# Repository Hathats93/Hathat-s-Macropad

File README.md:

# Hathats' Macropad

# Complete case with switches and keycaps installed

# Bare case (top and bottom)

# PCB schematic

# PCB layout

##  Bill of Materials/BOM
List of all parts used in my hackpad:

| Part | Quantity | Description | 
|------|----------|-------------|
| Mechanical Key Switches | 11 | MX-style switches |
| DSA Keycaps | 11 | Compatible with MX switches | 
| Seeed XIAO RP2040 | 1 | Microcontroller | 
| EC11 Rotary Encoder | 1 | Volume control | 
| PCB | 1 | Double-sided | 
| Case | 1 | 3D printed |

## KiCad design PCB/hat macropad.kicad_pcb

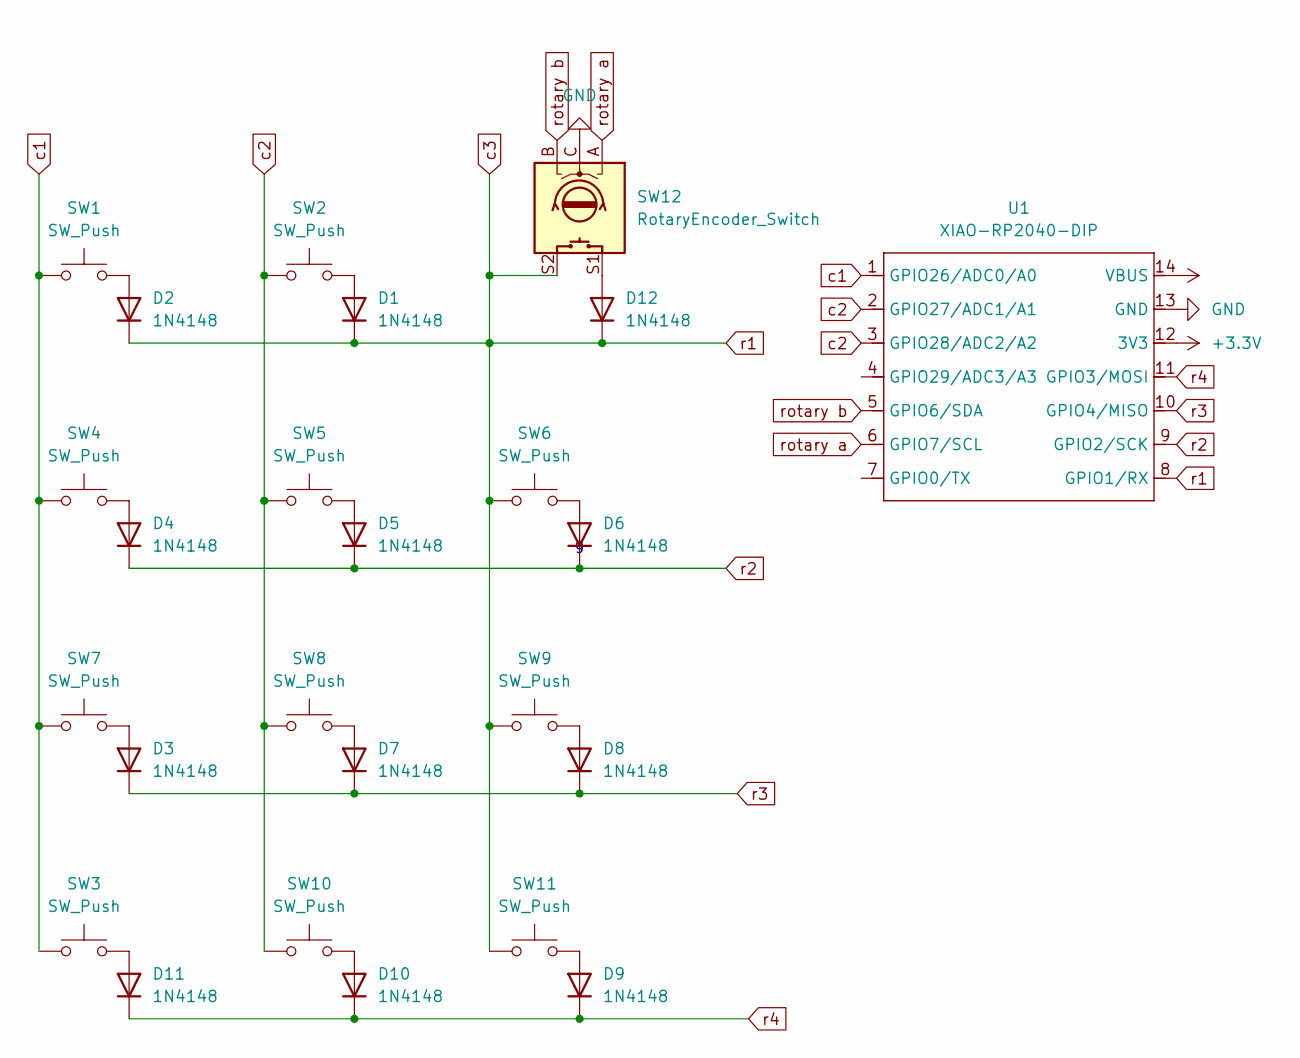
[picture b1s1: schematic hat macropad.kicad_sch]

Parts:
D1, D2, D3, D4, D5, D6, D7, D8, D9, D10, D11, D12: 1N4148; D_DO-35_SOD27_P7.62mm_Horizontal
SW1, SW2, SW3, SW4, SW5, SW6, SW7, SW8, SW9, SW10, SW11: SW_Push; SW_Cherry_MX_1.00u_PCB
SW12: RotaryEncoder_Switch; RotaryEncoder_Alps_EC11E-Switch_Vertical_H20mm
U1: XIAO-RP2040-DIP

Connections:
+3.3V: U1.12 (3V3)
+5V: U1.14 (VBUS)
GND: SW12.C, U1.13 (GND)
unnamed: D1.2 (A), SW2.2
unnamed: D2.2 (A), SW1.2
unnamed: D3.2 (A), SW7.2
unnamed: D4.2 (A), SW4.2
unnamed: D5.2 (A), SW5.2
unnamed: D6.2 (A), SW6.2
unnamed: D7.2 (A), SW8.2
unnamed: D8.2 (A), SW9.2
unnamed: D9.2 (A), SW11.2
unnamed: D10.2 (A), SW10.2
unnamed: D11.2 (A), SW3.2
unnamed: D12.2 (A), SW12.S1
c1: SW1.1, SW3.1, SW4.1, SW7.1, U1.1 (GPIO26/ADC0/A0)
c2: SW2.1, SW5.1, SW8.1, SW10.1, U1.2 (GPIO27/ADC1/A1), U1.3 (GPIO28/ADC2/A2)
c3: D1.1 (K), D2.1 (K), D12.1 (K), SW6.1, SW9.1, SW11.1, SW12.S2, U1.8 (GPIO1/RX)
r2: D4.1 (K), D5.1 (K), D6.1 (K), U1.9 (GPIO2/SCK)
r3: D3.1 (K), D7.1 (K), D8.1 (K), U1.10 (GPIO4/MISO)
r4: D9.1 (K), D10.1 (K), D11.1 (K), U1.11 (GPIO3/MOSI)
rotary a: SW12.A, U1.6 (GPIO7/SCL)
rotary b: SW12.B, U1.5 (GPIO6/SDA)

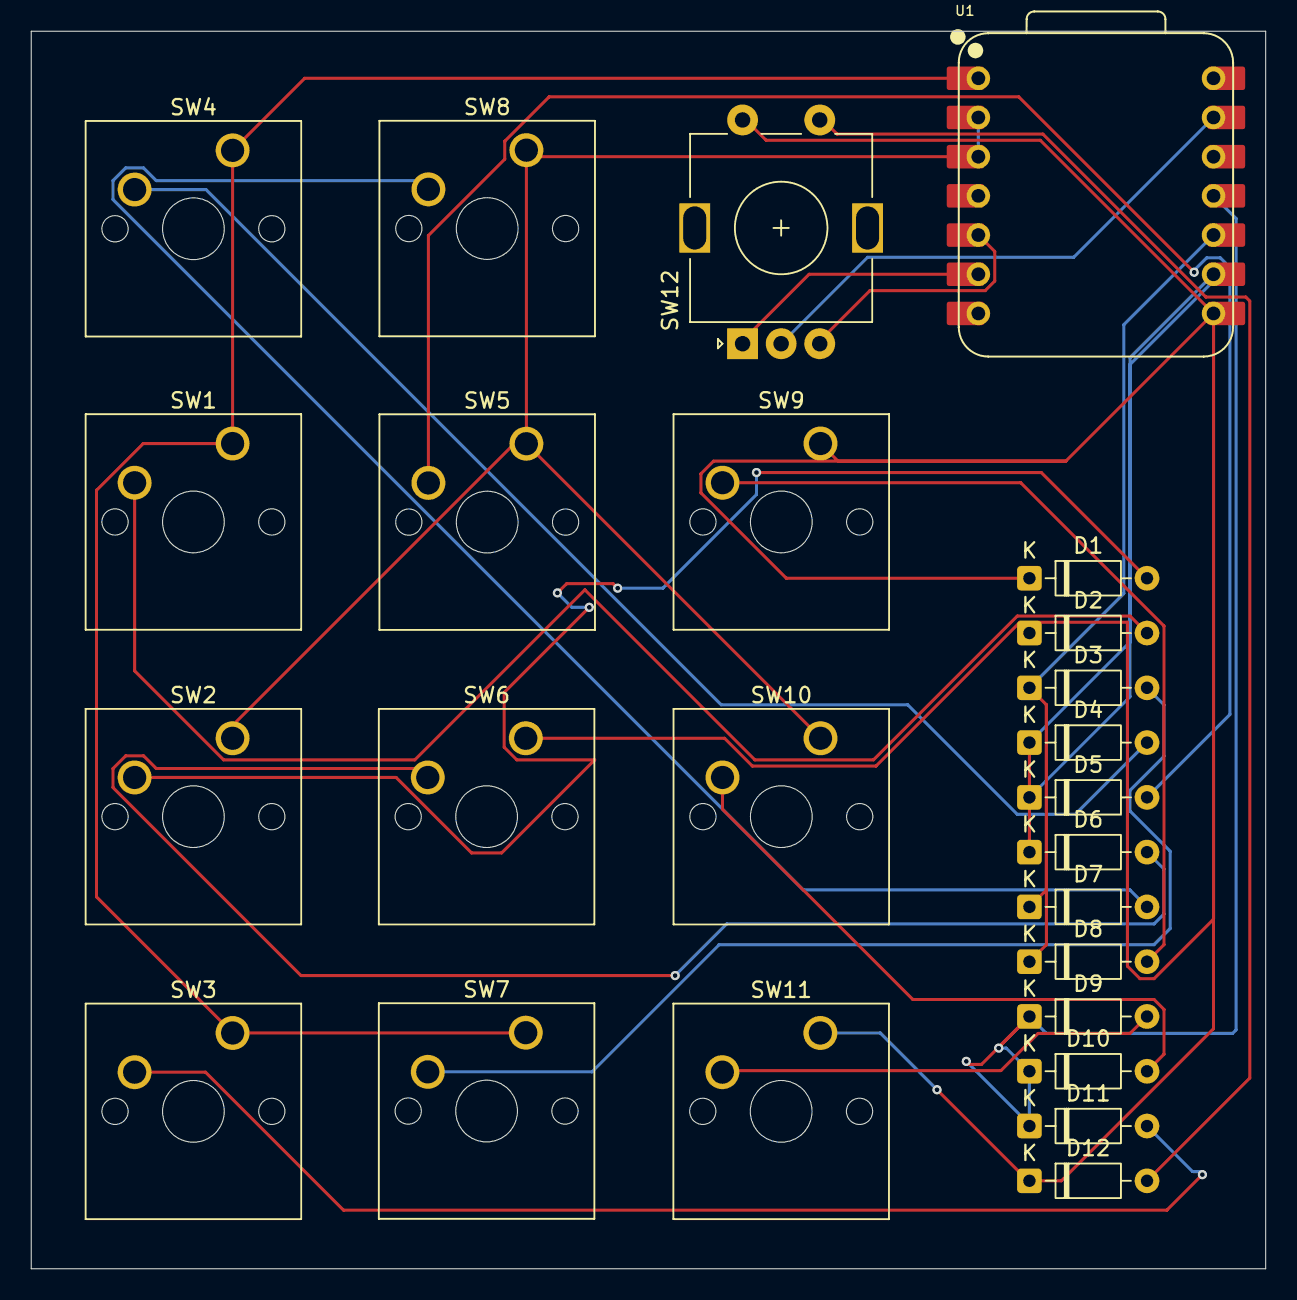
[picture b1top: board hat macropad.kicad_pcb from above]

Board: 2 copper layers, 80.0 x 80.2 mm, 25 parts (0 on the bottom side), 21 nets.

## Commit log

2026-01-30 Create Firmware
    Create kmk firmware for the Macropad
2026-01-30 Updated code Folder
    Updated code folder
2026-01-30 Updated file name
    Updated file name
2026-01-30 Added PCB code files
    Added pcb files from kikad
2026-01-30 Added Files
    Added Files
2026-02-04 removed switches from the STEP file
    removed switch and keycaps models
2026-02-04 Added optimized case step file
    changed case file
2026-02-04 removed file
    removed file
2026-02-05 added gerber files
    added gerber files
2026-02-05 added screenshot folder
2026-02-05 added new screenshots
2026-02-05 added case step with all components
2026-02-05 deleted old case step file
2026-02-05 added bare case
2026-02-05 compressed drl files
2026-02-05 Create fp-info-cache
2026-02-05 added production folder
2026-02-05 Added files to production folder
    added files to Production folder
